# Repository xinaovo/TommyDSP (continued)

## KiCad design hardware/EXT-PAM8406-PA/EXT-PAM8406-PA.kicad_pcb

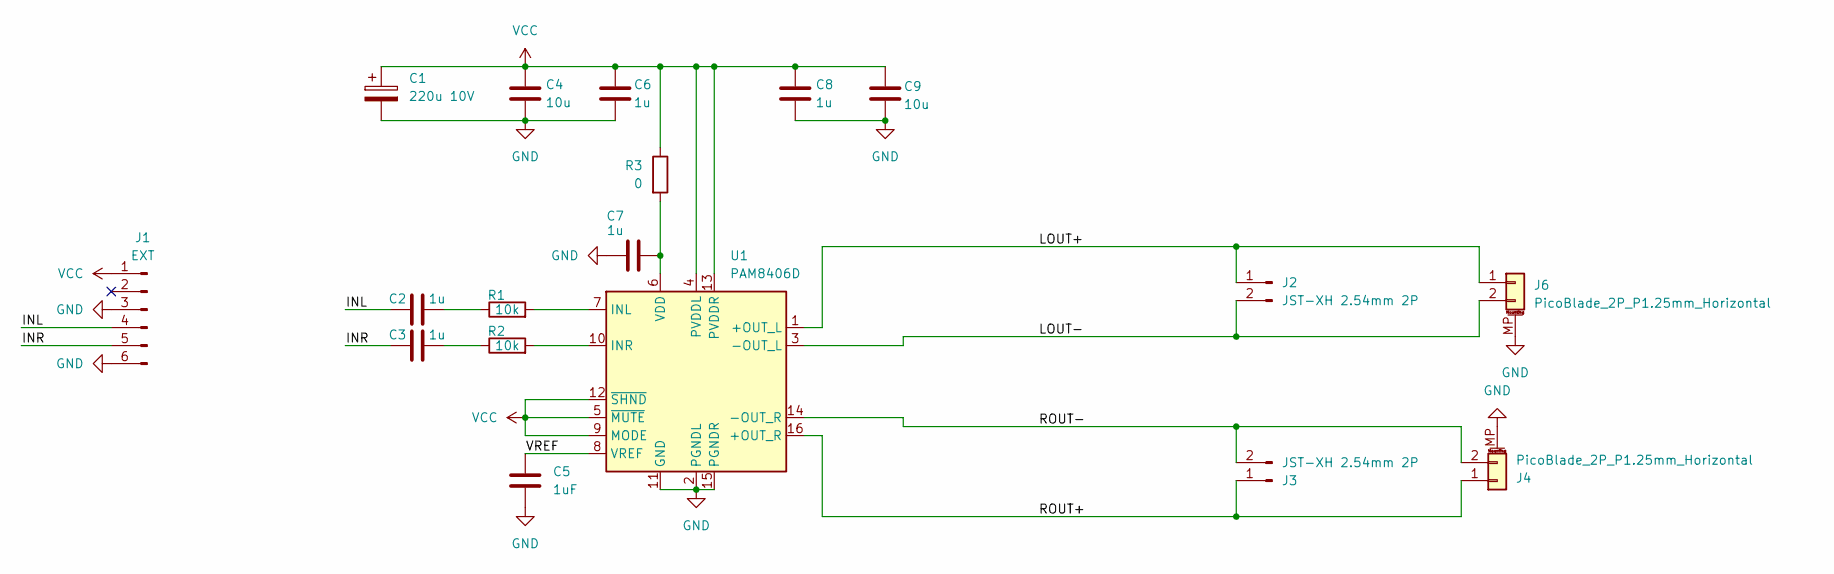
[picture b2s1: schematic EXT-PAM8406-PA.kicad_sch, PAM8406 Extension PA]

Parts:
C1: 220u 10V; C_Radial_D6.3mm_H7.0mm_P2.50mm
C2, C3, C6, C7, C8: 1u; C_0603_1608Metric
C4, C9: 10u; C_0603_1608Metric
C5: 1uF; C_0603_1608Metric
J1: EXT; JST_XH_S6B-XH-A-1_1x06_P2.50mm_Horizontal
J2, J3: JST-XH 2.54mm 2P; JST_XH_S2B-XH-A_1x02_P2.50mm_Horizontal
J4, J6: PicoBlade_2P_P1.25mm_Horizontal; Molex_PicoBlade_53261-0271_1x02-1MP_P1.25mm_Horizontal
R1, R2: 10k; R_0603_1608Metric
R3: 0; R_0603_1608Metric
U1: PAM8406D; SOIC-16_3.9x9.9mm_P1.27mm

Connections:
/INL: C2.1, J1.4
/INR: C3.1, J1.5
/LOUT+: J2.1, J6.1, U1.1 (+OUT_L)
/LOUT-: J2.2, J6.2, U1.3 (-OUT_L)
/ROUT+: J3.1, J4.1, U1.16 (+OUT_R)
/ROUT-: J3.2, J4.2, U1.14 (-OUT_R)
/VREF: C5.1, U1.8 (VREF)
GND: C1.2, C4.2, C5.2, C6.2, C7.1, C8.2, C9.2, J1.3, J1.6, J4.MP (MountPin), J6.MP (MountPin), U1.2 (PGNDL), U1.11 (GND), U1.15 (PGNDR)
unnamed: C2.2, R1.1
unnamed: C3.2, R2.1
unnamed: R1.2, U1.7 (INL)
unnamed: R2.2, U1.10 (INR)
unnamed: C7.2, R3.2, U1.6 (VDD)
VCC: C1.1, C4.1, C6.1, C8.1, C9.1, J1.1, R3.1, U1.4 (PVDDL), U1.5 (~MUTE), U1.9 (MODE), U1.12 (~SHND), U1.13 (PVDDR)

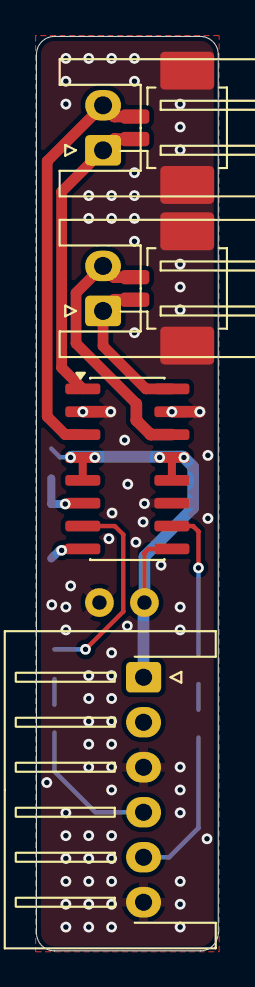
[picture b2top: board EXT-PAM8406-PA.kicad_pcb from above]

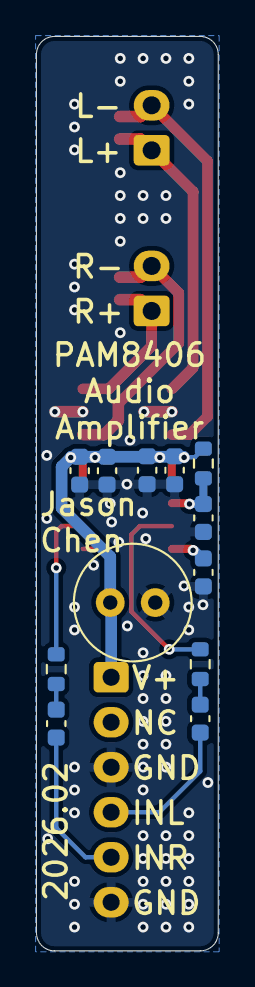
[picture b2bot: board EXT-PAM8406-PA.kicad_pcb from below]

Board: 2 copper layers, 10.1 x 50.8 mm, 18 parts (12 on the bottom side), 14 nets.

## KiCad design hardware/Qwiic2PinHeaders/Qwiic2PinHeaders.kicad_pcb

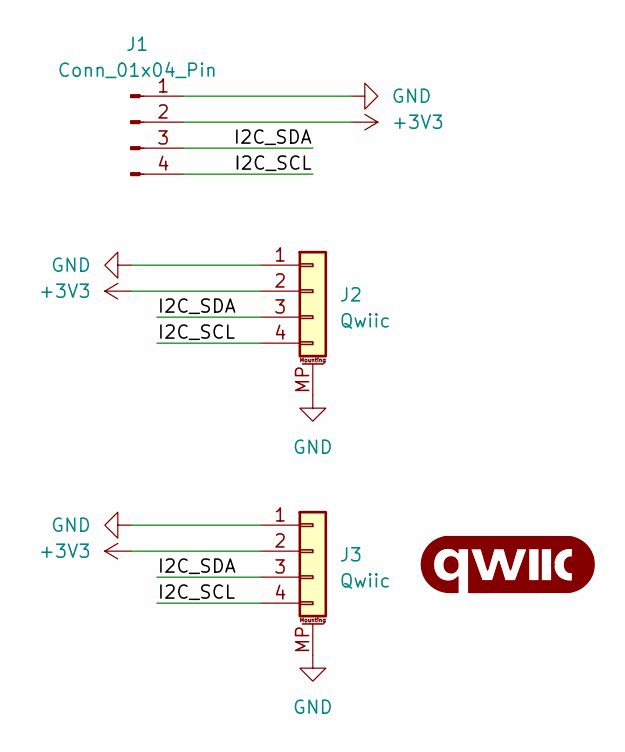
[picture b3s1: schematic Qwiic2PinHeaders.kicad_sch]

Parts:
G1: qwiic_Logo; qwiic_5.5mm
J1: Conn_01x04_Pin; PinHeader_1x04_P2.54mm_Vertical
J2, J3: Qwiic; JST_SH_SM04B-SRSS-TB_1x04-1MP_P1.00mm_Horizontal

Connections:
+3V3: J1.2, J2.2, J3.2
/I2C_SCL: J1.4, J2.4, J3.4
/I2C_SDA: J1.3, J2.3, J3.3
GND: J1.1, J2.1, J2.MP (MountPin), J3.1, J3.MP (MountPin)

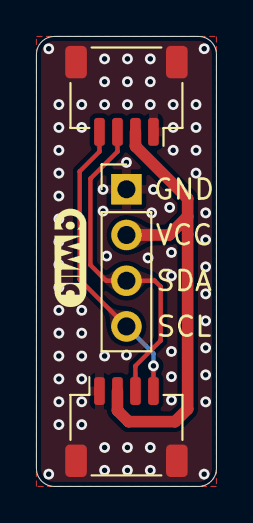
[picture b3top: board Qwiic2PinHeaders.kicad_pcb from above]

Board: 2 copper layers, 10.0 x 25.0 mm, 4 parts (0 on the bottom side), 4 nets.

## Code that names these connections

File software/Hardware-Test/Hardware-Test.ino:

#include <Adafruit_GFX.h>    // Core graphics library
#include <Adafruit_ST7735.h> // Hardware-specific library for ST7735
#include <SPI.h>

#define PIN_I2C_SCL 1
#define PIN_I2C_SDA 2

#define PIN_I2S_MCLK 7
#define PIN_I2S_BCLK 6
#define PIN_I2S_LRCK 5
#define PIN_I2S_DOUT 3
#define PIN_I2S_DIN 4

#define PIN_TFT_CS 9
#define PIN_TFT_DC 13
#define PIN_TFT_MOSI 11
#define PIN_TFT_SCK 10
#define PIN_TFT_RST 12
#define PIN_TFT_BL 8

#define PIN_SD_CLK_SCK 18
#define PIN_SD_CMD_MOSI 19
#define PIN_SD_DAT0_MISO 20
#define PIN_SD_DAT1 21
#define PIN_SD_DAT2 22
#define PIN_SD_DAT3_CS 23
#define PIN_SD_DET 24

#define PIN_PEDAL_1 14
#define PIN_PEDAL_2 15

#define PIN_ROTARY_ENCODER_CLK 16
#define PIN_ROTARY_ENCODER_DT 17
#define PIN_ROTARY_ENCODER_BUTTON 25

#define PIN_VBAT 26
#define PIN_KNOB_1 27
#define PIN_KNOB_2 28
#define PIN_KNOB_3 29

Adafruit_ST7735 tft = Adafruit_ST7735(&SPI1, PIN_TFT_CS, PIN_TFT_DC, PIN_TFT_RST);

void setup() {
  // put your setup code here, to run once:

  Serial.begin(9600);

  pinMode(PIN_PEDAL_1, INPUT);

  SPI1.setTX(PIN_TFT_MOSI);
  SPI1.setSCK(PIN_TFT_SCK);
  SPI1.setCS(PIN_TFT_CS);
  SPI1.setRX(NOPIN);
  tft.initR(INITR_BLACKTAB);      // Init ST7735S chip, black tab
  pinMode(PIN_TFT_BL, OUTPUT);
  digitalWrite(PIN_TFT_BL, HIGH); // Turn on LCD Backlight
  
}

void loop() {
  // put your main code here, to run repeatedly:
  lcd_test();
  // Serial.print("VBAT: ");
  // Serial.println(analogRead(PIN_VBAT), DEC);
  // Serial.print("KNOB1: ");
  // Serial.println(analogRead(PIN_KNOB_1), DEC);
  // Serial.print("KNOB2: ");
  // Serial.println(analogRead(PIN_KNOB_2), DEC);
  // Serial.print("KNOB3: ");
  // Serial.println(analogRead(PIN_KNOB_3), DEC);
  // delay(1000);
}

// LCD Test functions from AdafruitGFX examples
uint32_t i = 0;
void lcd_test(void){
  // tft print function!
  if(i % 100 == 0){
    tftPrintTest();
    delay(2000);
  }
  
  const uint16_t delay_time = 1;

  tft.fillScreen(ST77XX_BLACK);
  delay(delay_time);
  // large block of text
  tft.fillScreen(ST77XX_BLACK);
  testdrawtext("Lorem ipsum dolor sit amet, consectetur adipiscing elit. Curabitur adipiscing ante sed nibh tincidunt feugiat. Maecenas enim massa, fringilla sed malesuada et, malesuada sit amet turpis. Sed porttitor neque ut ante pretium vitae malesuada nunc bibendum. Nullam aliquet ultrices massa eu hendrerit. Ut sed nisi lorem. In vestibulum purus a tortor imperdiet posuere. ", ST77XX_WHITE);
  delay(delay_time);

  // a single pixel
  tft.drawPixel(tft.width()/2, tft.height()/2, ST77XX_GREEN);
  delay(delay_time);

  // line draw test
  testlines(ST77XX_YELLOW);
  delay(delay_time);

  // optimized lines
  testfastlines(ST77XX_RED, ST77XX_BLUE);
  delay(delay_time);

  testdrawrects(ST77XX_GREEN);
  delay(delay_time);

  testfillrects(ST77XX_YELLOW, ST77XX_MAGENTA);
  delay(delay_time);

  tft.fillScreen(ST77XX_BLACK);
  testfillcircles(10, ST77XX_BLUE);
  testdrawcircles(10, ST77XX_WHITE);
  delay(delay_time);

  testroundrects();
  delay(delay_time);

  testtriangles();
  delay(delay_time);

  i += 1;

}

void testlines(uint16_t color) {
  tft.fillScreen(ST77XX_BLACK);
  for (int16_t x=0; x < tft.width(); x+=6) {
    tft.drawLine(0, 0, x, tft.height()-1, color);
    delay(0);
  }
  for (int16_t y=0; y < tft.height(); y+=6) {
    tft.drawLine(0, 0, tft.width()-1, y, color);
    delay(0);
  }

  tft.fillScreen(ST77XX_BLACK);
  for (int16_t x=0; x < tft.width(); x+=6) {
    tft.drawLine(tft.width()-1, 0, x, tft.height()-1, color);
    delay(0);
  }
  for (int16_t y=0; y < tft.height(); y+=6) {
    tft.drawLine(tft.width()-1, 0, 0, y, color);
    delay(0);
  }

  tft.fillScreen(ST77XX_BLACK);
  for (int16_t x=0; x < tft.width(); x+=6) {
    tft.drawLine(0, tft.height()-1, x, 0, color);
    delay(0);
  }
  for (int16_t y=0; y < tft.height(); y+=6) {
    tft.drawLine(0, tft.height()-1, tft.width()-1, y, color);
    delay(0);
  }

  tft.fillScreen(ST77XX_BLACK);
  for (int16_t x=0; x < tft.width(); x+=6) {
    tft.drawLine(tft.width()-1, tft.height()-1, x, 0, color);
    delay(0);
  }
  for (int16_t y=0; y < tft.height(); y+=6) {
    tft.drawLine(tft.width()-1, tft.height()-1, 0, y, color);
    delay(0);
  }
}

void testdrawtext(char *text, uint16_t color) {
  tft.setCursor(0, 0);
  tft.setTextColor(color);
  tft.setTextWrap(true);
  tft.print(text);
}

void testfastlines(uint16_t color1, uint16_t color2) {
  tft.fillScreen(ST77XX_BLACK);
  for (int16_t y=0; y < tft.height(); y+=5) {
    tft.drawFastHLine(0, y, tft.width(), color1);
  }
  for (int16_t x=0; x < tft.width(); x+=5) {
    tft.drawFastVLine(x, 0, tft.height(), color2);
  }
}

void testdrawrects(uint16_t color) {
  tft.fillScreen(ST77XX_BLACK);
  for (int16_t x=0; x < tft.width(); x+=6) {
    tft.drawRect(tft.width()/2 -x/2, tft.height()/2 -x/2 , x, x, color);
  }
}

void testfillrects(uint16_t color1, uint16_t color2) {
  tft.fillScreen(ST77XX_BLACK);
  for (int16_t x=tft.width()-1; x > 6; x-=6) {
    tft.fillRect(tft.width()/2 -x/2, tft.height()/2 -x/2 , x, x, color1);
    tft.drawRect(tft.width()/2 -x/2, tft.height()/2 -x/2 , x, x, color2);
  }
}

void testfillcircles(uint8_t radius, uint16_t color) {
  for (int16_t x=radius; x < tft.width(); x+=radius*2) {
    for (int16_t y=radius; y < tft.height(); y+=radius*2) {
      tft.fillCircle(x, y, radius, color);
    }
  }
}

void testdrawcircles(uint8_t radius, uint16_t color) {
  for (int16_t x=0; x < tft.width()+radius; x+=radius*2) {
    for (int16_t y=0; y < tft.height()+radius; y+=radius*2) {
      tft.drawCircle(x, y, radius, color);
    }
  }
}

void testtriangles() {
  tft.fillScreen(ST77XX_BLACK);
  uint16_t color = 0xF800;
  int t;
  int w = tft.width()/2;
  int x = tft.height()-1;
  int y = 0;
  int z = tft.width();
  for(t = 0 ; t <= 15; t++) {
    tft.drawTriangle(w, y, y, x, z, x, color);
    x-=4;
    y+=4;
    z-=4;
    color+=100;
  }
}

void testroundrects() {
  tft.fillScreen(ST77XX_BLACK);
  uint16_t color = 100;
  int i;
  int t;
  for(t = 0 ; t <= 4; t+=1) {
    int x = 0;
    int y = 0;
    int w = tft.width()-2;
    int h = tft.height()-2;
    for(i = 0 ; i <= 16; i+=1) {
      tft.drawRoundRect(x, y, w, h, 5, color);
      x+=2;
      y+=3;
      w-=4;
      h-=6;
      color+=1100;
    }
    color+=100;
  }
}

void tftPrintTest() {
  const float p = 3.1415926;
  tft.setTextWrap(false);
  tft.fillScreen(ST77XX_BLACK);
  tft.setCursor(0, 30);
  tft.setTextColor(ST77XX_RED);
  tft.setTextSize(1);
  tft.println("Hello World!");
  tft.setTextColor(ST77XX_YELLOW);
  tft.setTextSize(2);
  tft.println("Hello World!");
  tft.setTextColor(ST77XX_GREEN);
  tft.setTextSize(3);
  tft.println("Hello World!");
  tft.setTextColor(ST77XX_BLUE);
  tft.setTextSize(4);
  tft.print(1234.567);
  delay(1500);
  tft.setCursor(0, 0);
  tft.fillScreen(ST77XX_BLACK);
  tft.setTextColor(ST77XX_WHITE);
  tft.setTextSize(0);
  tft.println("Hello World!");
  tft.setTextSize(1);
  tft.setTextColor(ST77XX_GREEN);
  tft.print(p, 6);
  tft.println(" Want pi?");
  tft.println(" ");
  tft.print(8675309, HEX); // print 8,675,309 out in HEX!
  tft.println(" Print HEX!");
  tft.println(" ");
  tft.setTextColor(ST77XX_WHITE);
  tft.println("Sketch has been");
  tft.println("running for: ");
  tft.setTextColor(ST77XX_MAGENTA);
  tft.print(millis() / 1000);
  tft.setTextColor(ST77XX_WHITE);
  tft.print(" seconds.");
}

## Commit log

2026-01-31 add Microcontroller circuit
2026-02-06 add demo sketches, DAC works now but MIC doesn't work
2026-02-09 misc: update .gitignore
2026-02-10 hardware: finished PCB routing
2026-02-11 hardware: finalize PCB design
2026-02-11 hardware: minor silkscreen text adjustments
2026-02-12 hardware: fix incorrect audio jack symbol
2026-02-12 hardware: minor tweaks
2026-02-13 hardware: adjust value of BUCK feedback resistors
2026-02-13 software: add loopback demo
2026-02-13 hardware: add compatibility for WM8988 CODEC
2026-02-13 hardware: modified audio page notes
2026-02-16 hardware: add PAM8406 audio amplifier board
2026-02-16 hardware: add Quiic2PinHeaders
2026-02-16 hardware: add USON2SOIC-8
2026-02-16 hardware: change cooper pour thermal relief settings for Qwiic2PinHeaders
2026-02-27 hardware: add misc project files
2026-02-27 software: add delay effect demo
2026-02-27 software: add pitch shift effect demo
2026-02-27 software: add custom frequency-modulation-like pitch shift effect demo
2026-02-27 software: minor change to I2S loopback demo
2026-03-06 minor PCB optimization
2026-03-06 software: add ST7735 1.8' LCD Demo
2026-03-06 Create dynamic audio stream class rewrite?
2026-03-12 add pitch shifting recorder
2026-03-13 add SkeakingTom sketch
2026-03-13 sync local tree
2026-04-24 bump to KiCad V10, add logo
